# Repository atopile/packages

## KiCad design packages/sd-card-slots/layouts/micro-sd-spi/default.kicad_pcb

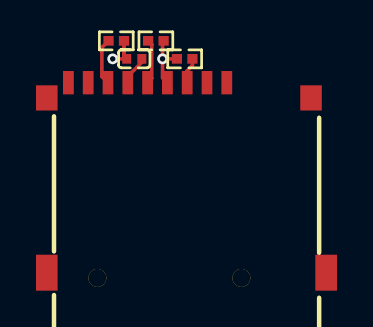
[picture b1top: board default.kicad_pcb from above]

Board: 2 copper layers, 5 parts (0 on the bottom side), 5 nets.

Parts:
C1: 100nF; C0402
Card1: TF-SMD_TF-01A
R1, R2, R3: 10kΩ; R0402

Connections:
MISO: Card1.7, R1.1
MOSI: Card1.3, R2.1
SCLK: Card1.5, R3.1
hv: C1.1, Card1.4, R1.2, R2.2, R3.2
lv: C1.2, Card1.6, Card1.10, Card1.11, Card1.12, Card1.13

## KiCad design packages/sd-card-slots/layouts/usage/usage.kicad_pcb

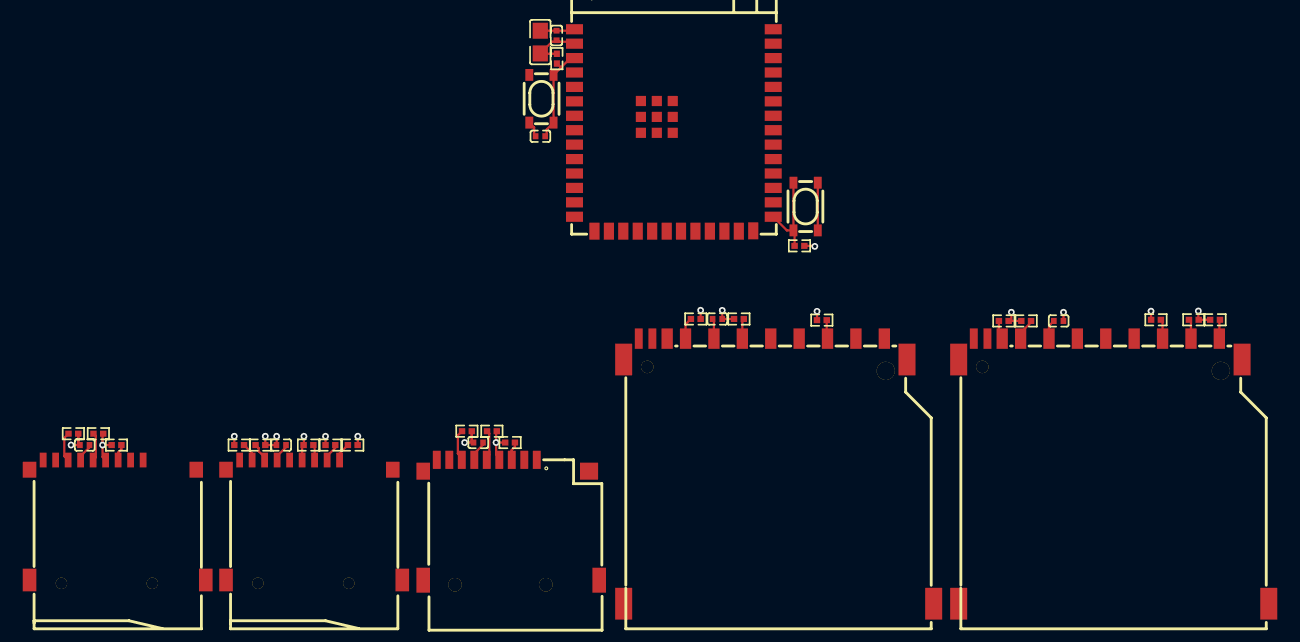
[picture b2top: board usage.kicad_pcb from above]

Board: 2 copper layers, 37 parts (0 on the bottom side), 24 nets.

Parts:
C1, C2, C4, C6, C7, C8: 100nF; C0402
C3: 10µF; C0805
C5: 1µF; C0402
Card1, Card2: SIM-SMD_SD-102
Card3, Card5: TF-SMD_TF-01A
Card4: TF-SMD_TF-PUSH
R1, R2, R3, R4, R5, R6, R7, R8, R9, R10, R11, R12, R13, R14, R15, R16, R17, R18, R19, R20, R21: 10kΩ; R0402
SW1, SW2: KEY-SMD_4P-L4.2-W3.2-P2.20-LS4.6
U1: WIRELM-SMD_ESP32-S3-WROOM-1

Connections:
CMD: Card1.2, R1.1
MISO: Card2.7, R6.1
MOSI: Card2.2, R7.1
SCLK: Card2.5, R8.1
hv: C1.1, C2.1, C3.1, C4.1, C6.1, C7.1, C8.1, Card1.4, Card2.4, Card3.4, Card4.4, Card5.4, R1.2, R2.2, R3.2, R4.2, R5.2, R6.2, R7.2, R8.2, R9.1, R10.1, R11.2, R12.2, R13.2, R14.2, R15.2, R16.2, R17.2, R18.2, R19.2, R20.2, R21.2, U1.2
line: Card5.2, U1.18
lv: C1.2, C2.2, C3.2, C4.2, C5.2, C6.2, C7.2, C8.2, Card1.3, Card1.6, Card1.12, Card1.13, Card1.14, Card1.15, Card2.3, Card2.6, Card2.12, Card2.13, Card2.14, Card2.15, Card3.6, Card3.10, Card3.11, Card3.12, Card3.13, Card4.6, Card5.6, Card5.10, Card5.11, Card5.12, Card5.13, SW1.1, SW1.2, SW2.1, SW2.2, U1.1, U1.40, U1.41
output: R9.2, SW1.3, SW1.4, U1.27
pins[0]: Card1.1, R5.1
pins[6]: Card1.7, R2.1
pins[7]: Card1.8, R3.1
pins[8]: Card1.9, R4.1
power-hv: C5.1, R10.2, SW2.3, SW2.4, U1.3
transport-sd-CMD: Card3.3, R11.1
transport-sd-pins[0]: Card3.2, R15.1
transport-sd-pins[6]: Card3.7, R12.1
transport-sd-pins[7]-1: Card3.8, R13.1
transport-sd-pins[8]-1: Card3.1, R14.1
transport-spi-MISO: Card5.7, R19.1, U1.21
transport-spi-MISO-1: Card4.7, R16.1
transport-spi-MOSI: Card5.3, R20.1, U1.19
transport-spi-MOSI-1: Card4.3, R17.1
transport-spi-SCLK: Card5.5, R21.1, U1.20
transport-spi-SCLK-1: Card4.5, R18.1
